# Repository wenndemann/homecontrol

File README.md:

# homecontrol
setup of my home automation

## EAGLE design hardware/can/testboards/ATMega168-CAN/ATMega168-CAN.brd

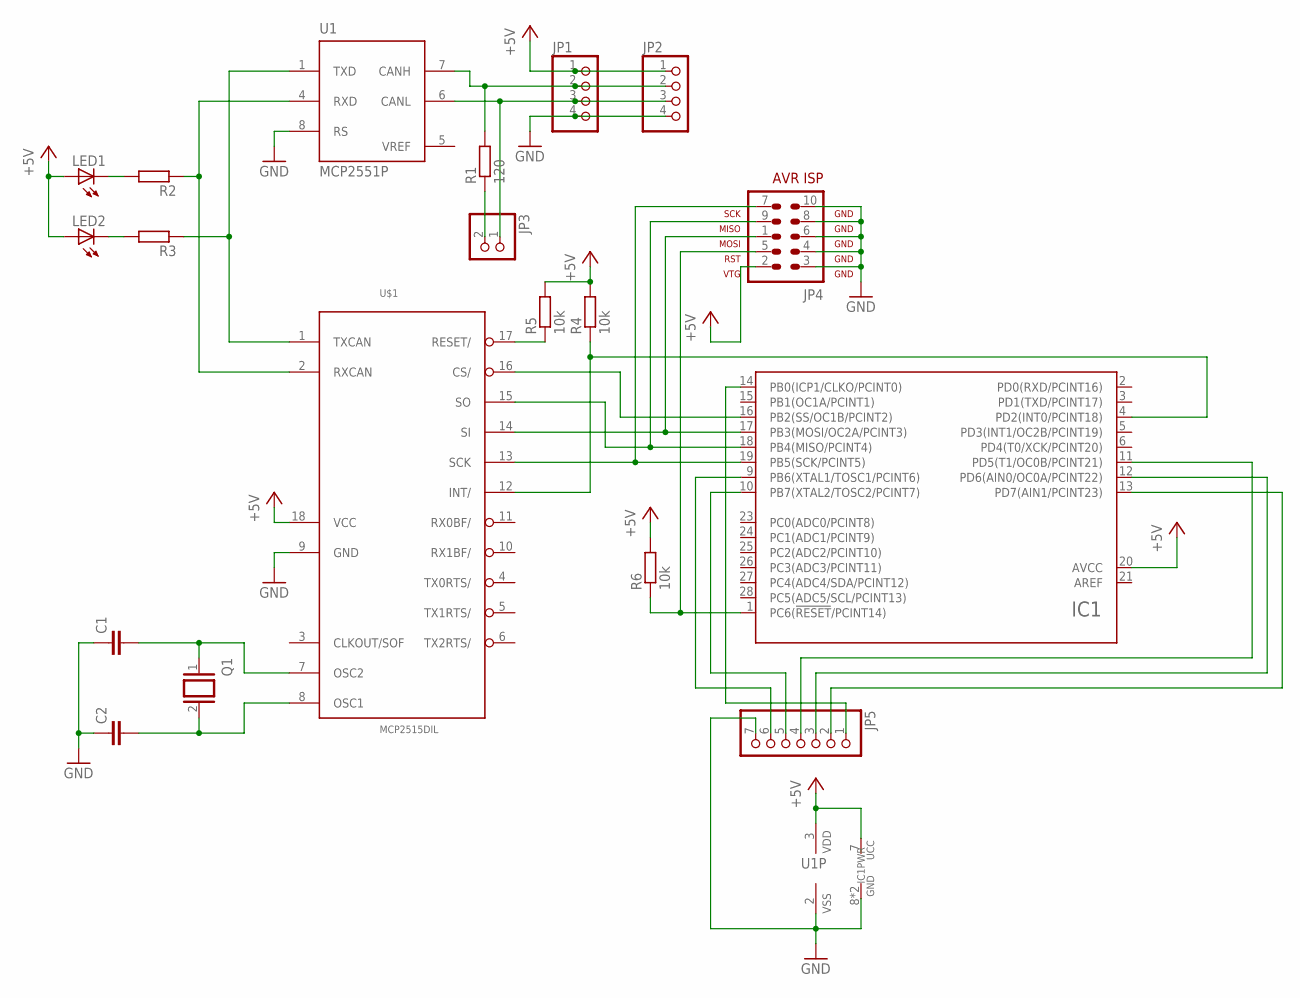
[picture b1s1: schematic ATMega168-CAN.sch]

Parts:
C1, C2: C-EU025-024X044; C025-024X044
IC1: ATMEGA48/88/168/328-PU(DIP28)PU; DIL28
JP1, JP2: PINHD-1X4/90; 1X04/90
JP3: PINHD-1X2; 1X02
JP4: AVR-ISP-10
JP5: PINHD-1X7; 1X07
LED1, LED2: LED5MM
Q1: XTAL/S; QS
R1: 120; 0207/10
R2, R3: R-EU_0207/10; 0207/10
R4, R5, R6: 10k; 0207/10
U1: MCP2551P; DIL8
U$1: MCP2515DIL; DIL18

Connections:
+5V: IC1.7 (UCC), IC1.20 (AVCC), JP1.1, JP2.1, JP4.2, LED1.A, LED2.A, R4.2, R5.2, R6.2, U1.3 (VDD), U$1.18 (VCC)
GND: C1.1, C2.1, IC1.8 (GND), IC1.22 (GND), JP1.4, JP2.4, JP4.3, JP4.4, JP4.6, JP4.8, JP4.10, JP5.7, U1.2 (VSS), U1.8 (RS), U$1.9 (GND)
unnamed: C2.2, Q1.2, U$1.8 (OSC1)
unnamed: C1.2, Q1.1, U$1.7 (OSC2)
unnamed: JP1.2, JP2.2, R1.2, U1.7 (CANH)
unnamed: JP1.3, JP2.3, JP3.1, U1.6 (CANL)
unnamed: IC1.4 (PD2(INT0/PCINT18)), R4.1, U$1.12 (INT/)
unnamed: IC1.19 (PB5(SCK/PCINT5)), JP4.7, U$1.13 (SCK)
unnamed: JP3.2, R1.1
unnamed: IC1.17 (PB3(MOSI/OC2A/PCINT3)), JP4.1, U$1.14 (SI)
unnamed: IC1.18 (PB4(MISO/PCINT4)), JP4.9, U$1.15 (SO)
unnamed: IC1.16 (PB2(SS/OC1B/PCINT2)), U$1.16 (CS/)
unnamed: R3.1, U1.1 (TXD), U$1.1 (TXCAN)
unnamed: R2.1, U1.4 (RXD), U$1.2 (RXCAN)
unnamed: LED1.K (C), R2.2
unnamed: LED2.K (C), R3.2
unnamed: R5.1, U$1.17 (RESET/)
unnamed: IC1.1 (PC6(!RESET!/PCINT14)), JP4.5, R6.1
unnamed: IC1.9 (PB6(XTAL1/TOSC1/PCINT6)), JP5.6
unnamed: IC1.10 (PB7(XTAL2/TOSC2/PCINT7)), JP5.5
unnamed: IC1.11 (PD5(T1/OC0B/PCINT21)), JP5.4
unnamed: IC1.12 (PD6(AIN0/OC0A/PCINT22)), JP5.3
unnamed: IC1.13 (PD7(AIN1/PCINT23)), JP5.2
unnamed: IC1.14 (PB0(ICP1/CLKO/PCINT0)), JP5.1
VREF: U1.5 (VREF)

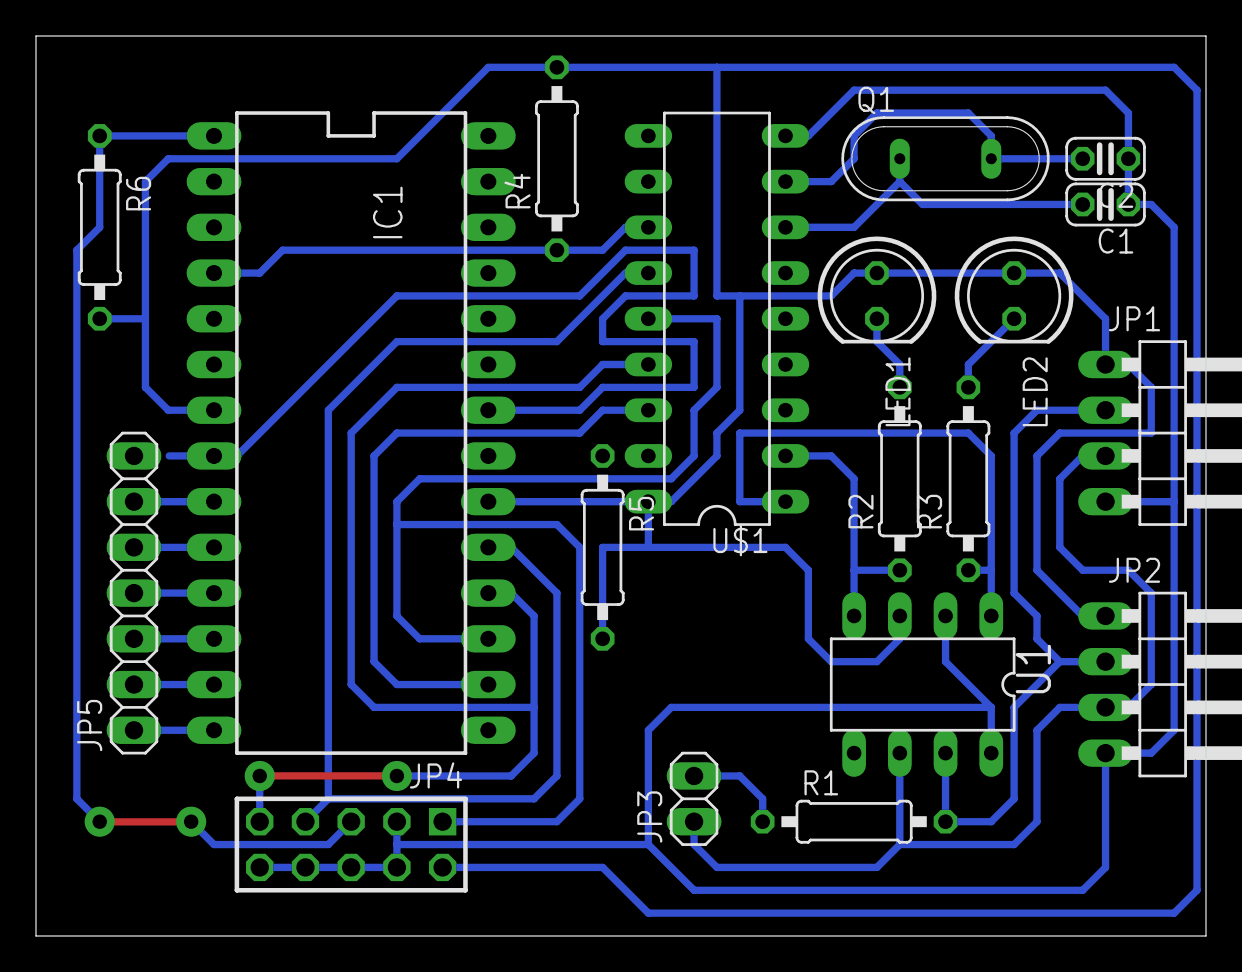
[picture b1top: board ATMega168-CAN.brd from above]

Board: 2 copper layers, 65.0 x 50.0 mm, 19 parts (0 on the bottom side), 24 nets.

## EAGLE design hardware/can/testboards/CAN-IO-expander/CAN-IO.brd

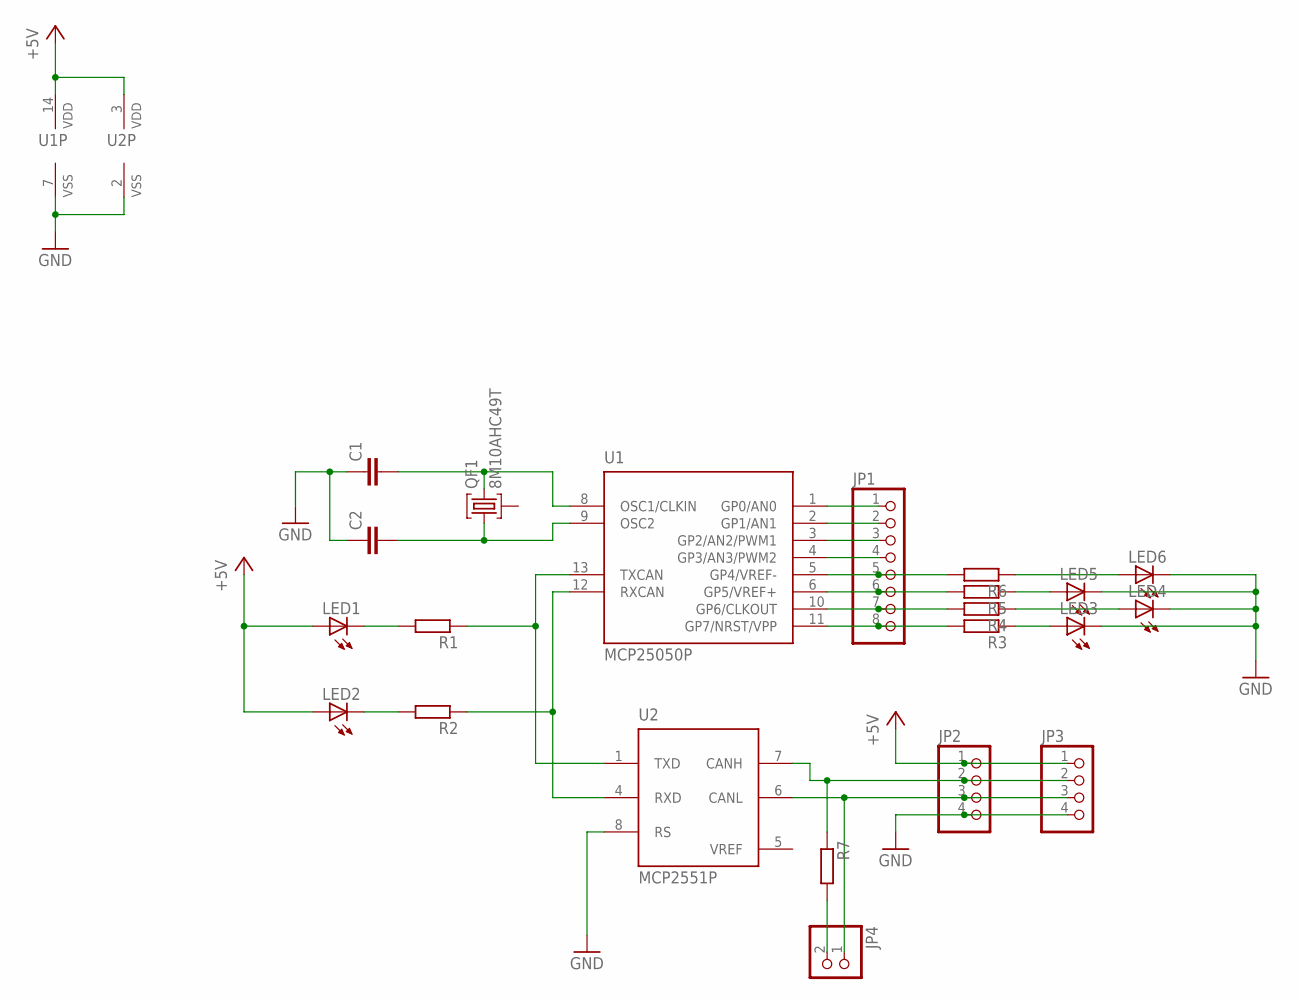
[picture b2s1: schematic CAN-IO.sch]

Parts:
C1, C2: C-EU025-024X044; C025-024X044
JP1: PINHD-1X8; 1X08
JP2, JP3: PINHD-1X4/90; 1X04/90
JP4: PINHD-1X2; 1X02
LED1, LED2, LED3, LED4, LED5, LED6: LED5MM
QF1: 8M10AHC49T; HC49U
R1, R2, R3, R4, R5, R6, R7: R-EU_0207/10; 0207/10
U1: MCP25050P; DIL14
U2: MCP2551P; DIL8

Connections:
+5V: JP2.1, JP3.1, LED1.A, LED2.A, U1.14 (VDD), U2.3 (VDD)
GND: C1.1, C2.1, JP2.4, JP3.4, LED3.K (C), LED4.K (C), LED5.K (C), LED6.K (C), U1.7 (VSS), U2.2 (VSS), U2.8 (RS)
unnamed: R1.1, U1.13 (TXCAN), U2.1 (TXD)
unnamed: R2.1, U1.12 (RXCAN), U2.4 (RXD)
unnamed: LED1.K (C), R1.2
unnamed: LED2.K (C), R2.2
unnamed: LED3.A, R3.1
unnamed: JP1.1, U1.1 (GP0/AN0)
unnamed: JP1.2, U1.2 (GP1/AN1)
unnamed: JP1.3, U1.3 (GP2/AN2/PWM1)
unnamed: JP1.4, U1.4 (GP3/AN3/PWM2)
unnamed: JP1.5, R6.2, U1.5 (GP4/VREF-)
unnamed: JP1.6, R5.2, U1.6 (GP5/VREF+)
unnamed: JP1.7, R4.2, U1.10 (GP6/CLKOUT)
unnamed: JP1.8, R3.2, U1.11 (GP7/NRST/VPP)
unnamed: LED5.A, R5.1
unnamed: LED4.A, R4.1
unnamed: LED6.A, R6.1
unnamed: C1.2, QF1.3, U1.8 (OSC1/CLKIN)
unnamed: C2.2, QF1.1, U1.9 (OSC2)
unnamed: JP2.3, JP3.3, JP4.1, U2.6 (CANL)
unnamed: JP2.2, JP3.2, R7.1, U2.7 (CANH)
unnamed: JP4.2, R7.2
VREF: U2.5 (VREF)

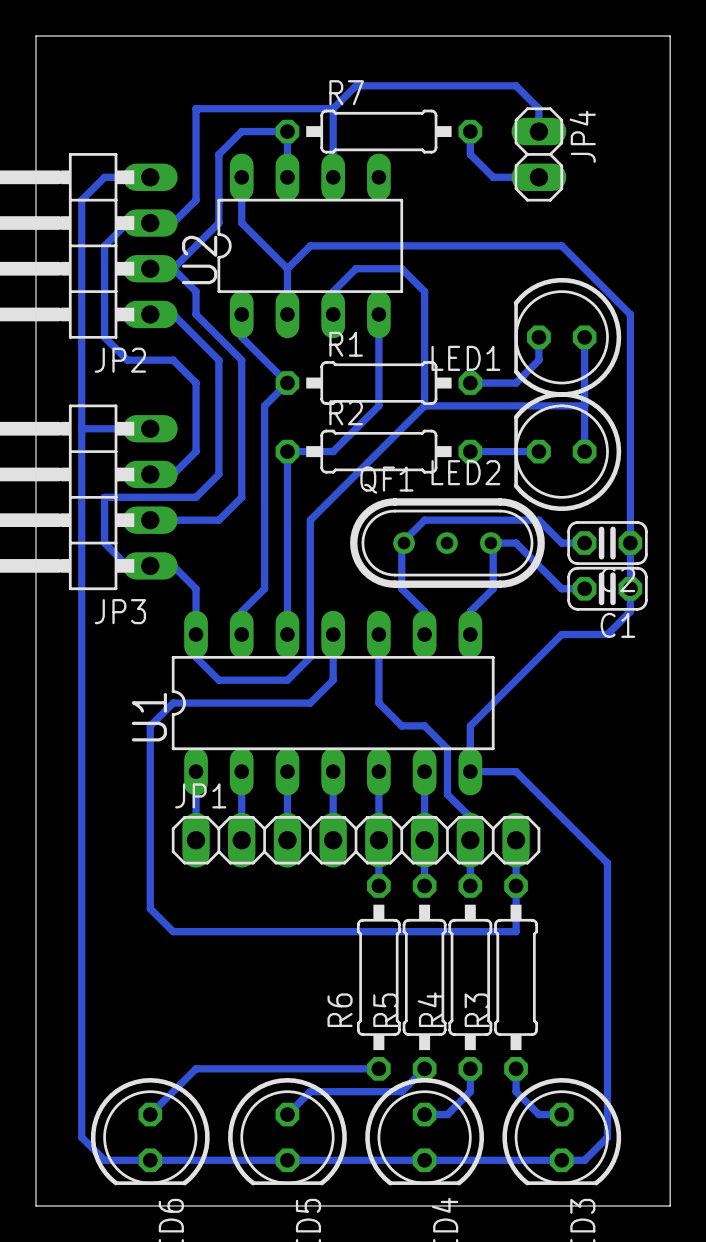
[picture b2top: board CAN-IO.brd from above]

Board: 2 copper layers, 35.2 x 65.0 mm, 22 parts (0 on the bottom side), 23 nets.

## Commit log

2015-03-05 CAN-Bus test boards initial commit
